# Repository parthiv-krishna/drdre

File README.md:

# drdre
Distributed and Reconfigurable Drove of Redundant Executors

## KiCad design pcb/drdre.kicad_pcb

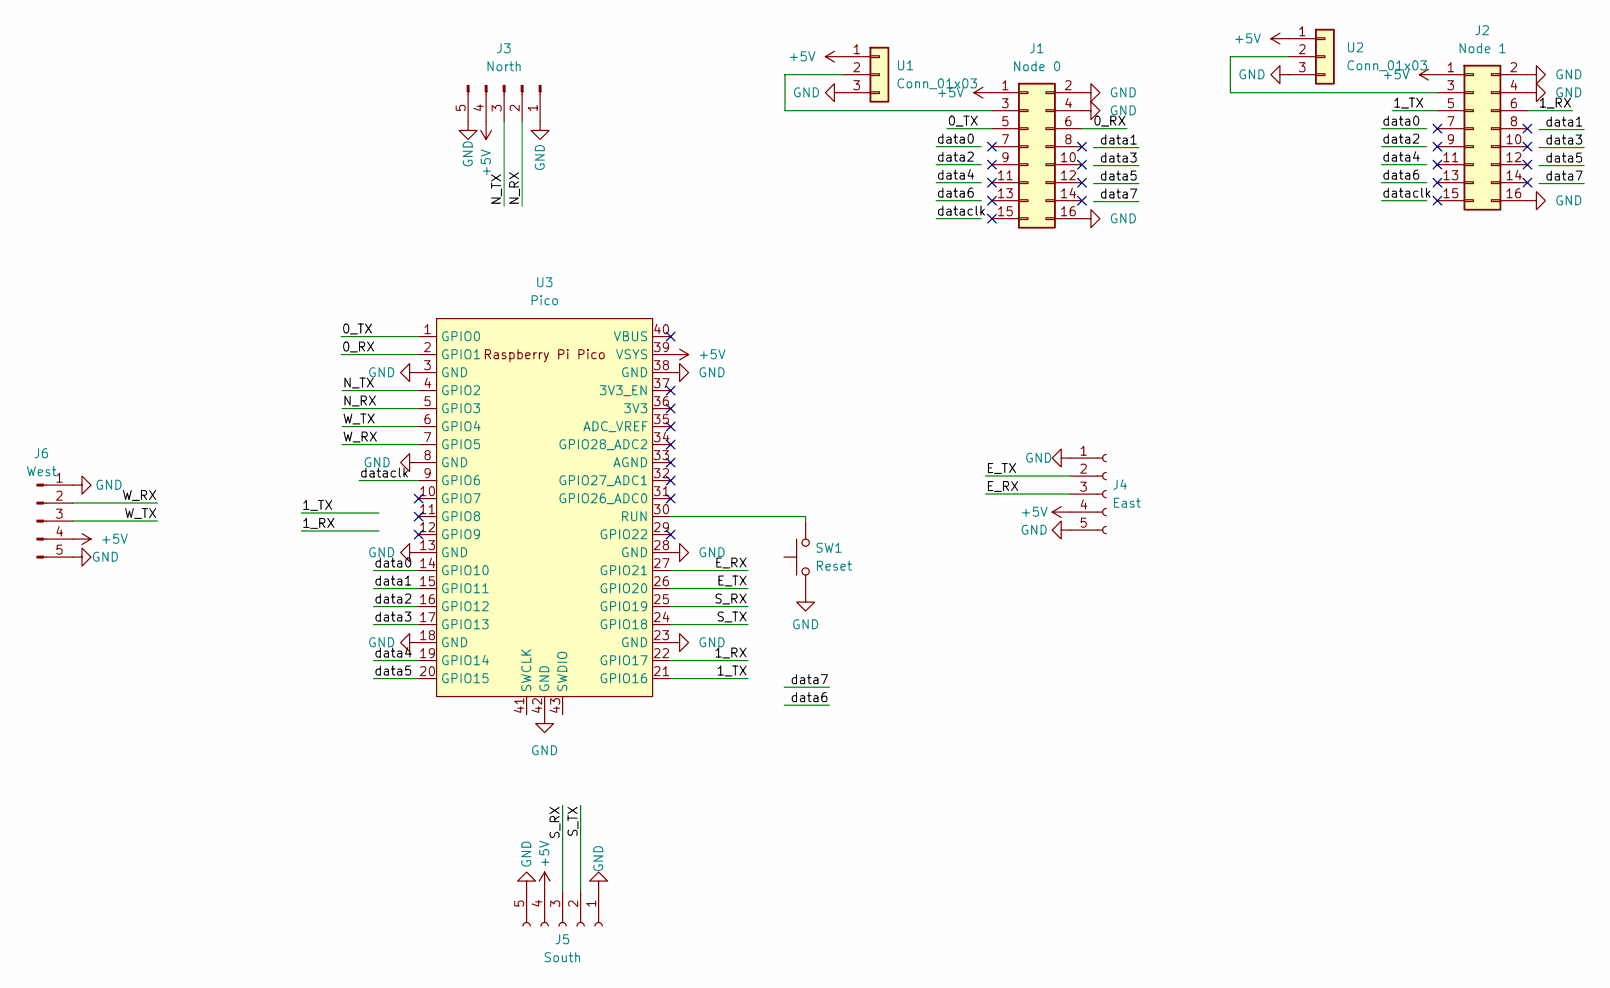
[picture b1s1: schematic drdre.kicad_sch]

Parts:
J1: Node 0; PinSocket_2x08_P2.54mm_Vertical
J2: Node 1; PinSocket_2x08_P2.54mm_Vertical
J3: North; PinHeader_1x05_P2.54mm_Horizontal
J4: East; PinSocket_1x05_P2.54mm_Horizontal
J5: South; PinSocket_1x05_P2.54mm_Horizontal
J6: West; PinHeader_1x05_P2.54mm_Horizontal
SW1: Reset
U1, U2: Conn_01x03; PinSocket_1x03_P2.54mm_Vertical
U3: Pico; RPi_Pico_SMD_TH

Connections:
+5V: J1.1, J2.1, J3.4, J4.4, J5.4, J6.4, U1.1, U2.1, U3.39 (VSYS)
/0_RX: J1.6, U3.2 (GPIO1)
/0_TX: J1.5, U3.1 (GPIO0)
/1_RX: J2.6, U3.22 (GPIO17)
/1_TX: J2.5, U3.21 (GPIO16)
/E_RX: J4.3, U3.27 (GPIO21)
/E_TX: J4.2, U3.26 (GPIO20)
/N_RX: J3.2, U3.5 (GPIO3)
/N_TX: J3.3, U3.4 (GPIO2)
/S_RX: J5.3, U3.25 (GPIO19)
/S_TX: J5.2, U3.24 (GPIO18)
/W_RX: J6.2, U3.7 (GPIO5)
/W_TX: J6.3, U3.6 (GPIO4)
/data0: U3.14 (GPIO10)
/data1: U3.15 (GPIO11)
/data2: U3.16 (GPIO12)
/data3: U3.17 (GPIO13)
/data4: U3.19 (GPIO14)
/data5: U3.20 (GPIO15)
/dataclk: U3.9 (GPIO6)
GND: J1.2, J1.4, J1.16, J2.2, J2.4, J2.16, J3.1, J3.5, J4.1, J4.5, J5.1, J5.5, J6.1, J6.5, SW1.1, U1.3, U2.3, U3.3 (GND), U3.8 (GND), U3.13 (GND), U3.18 (GND), U3.23 (GND), U3.28 (GND), U3.38 (GND), U3.42 (GND)
unnamed: J1.3, U1.2
unnamed: J2.3, U2.2
unnamed: SW1.2, U3.30 (RUN)

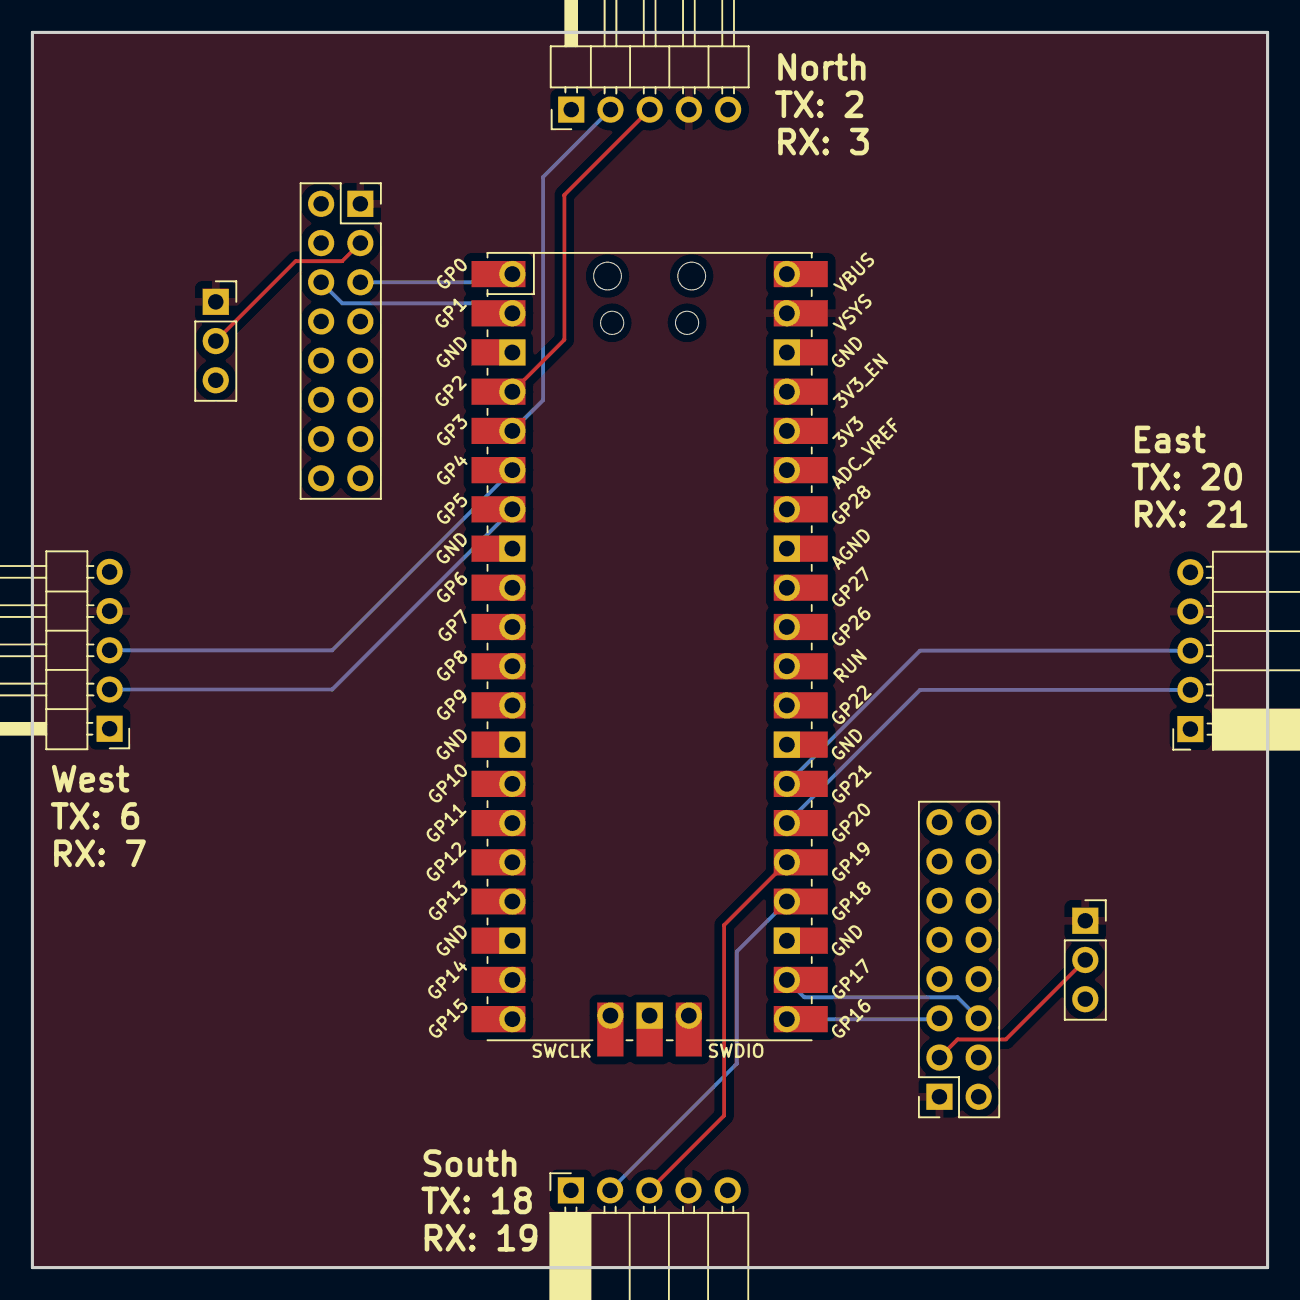
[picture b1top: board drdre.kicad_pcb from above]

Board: 2 copper layers, 80.0 x 80.0 mm, 9 parts (0 on the bottom side), 16 nets.

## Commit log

2024-02-20 KiCad-RP-Pico submodule
2024-02-20 kicad project init
2024-02-20 v2: mesh network
